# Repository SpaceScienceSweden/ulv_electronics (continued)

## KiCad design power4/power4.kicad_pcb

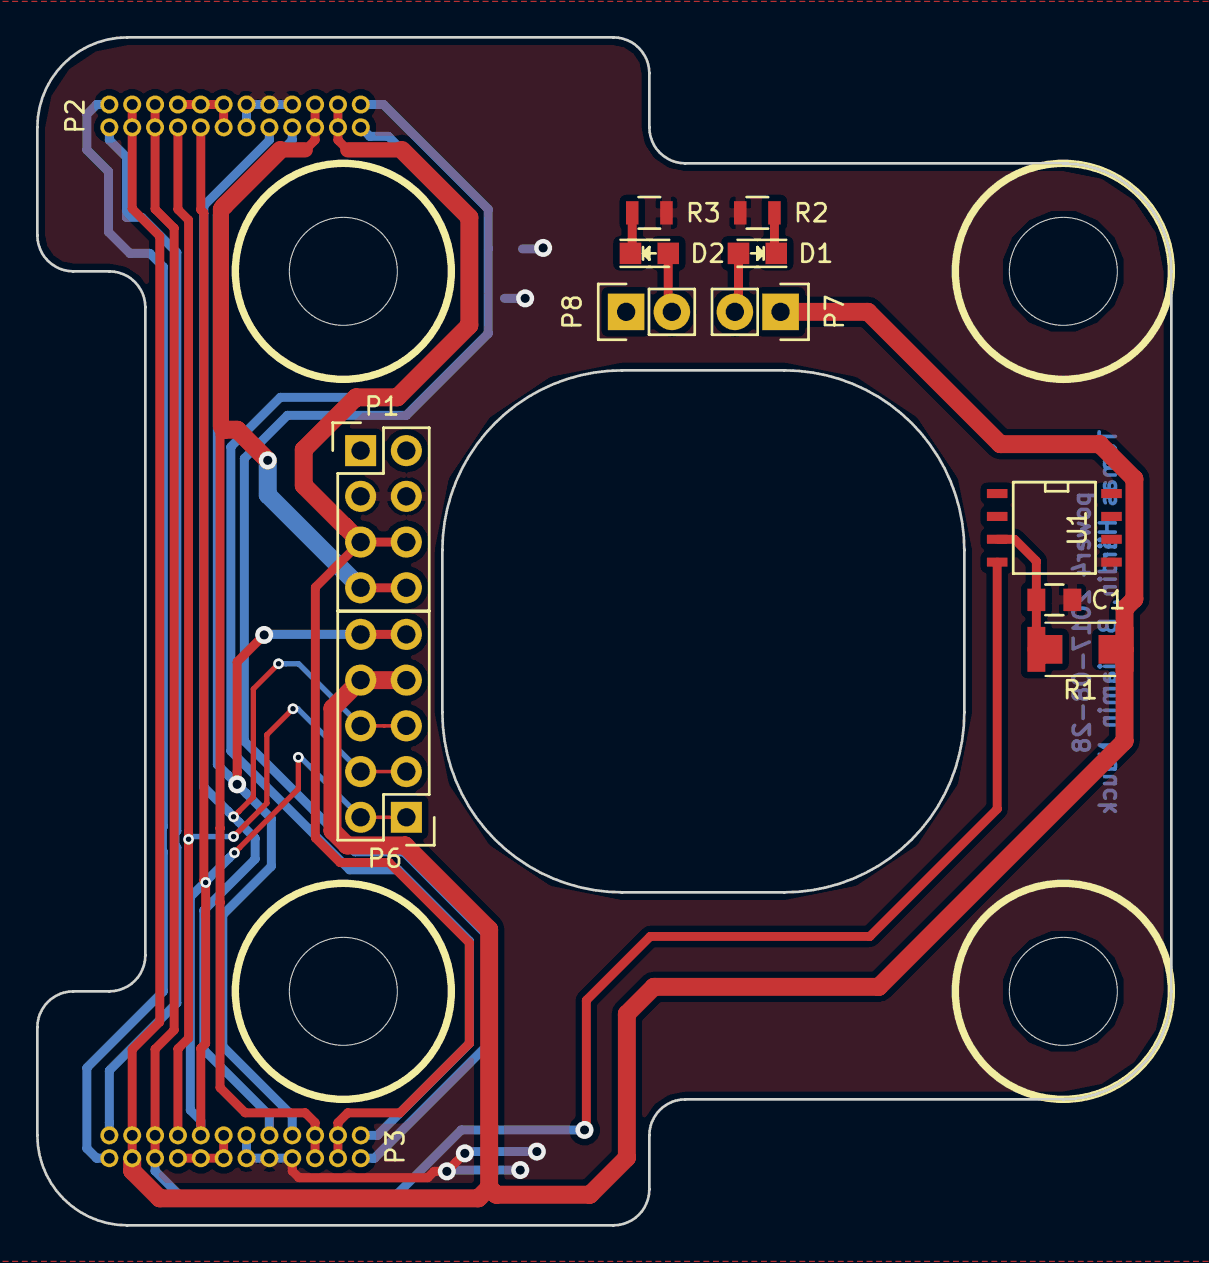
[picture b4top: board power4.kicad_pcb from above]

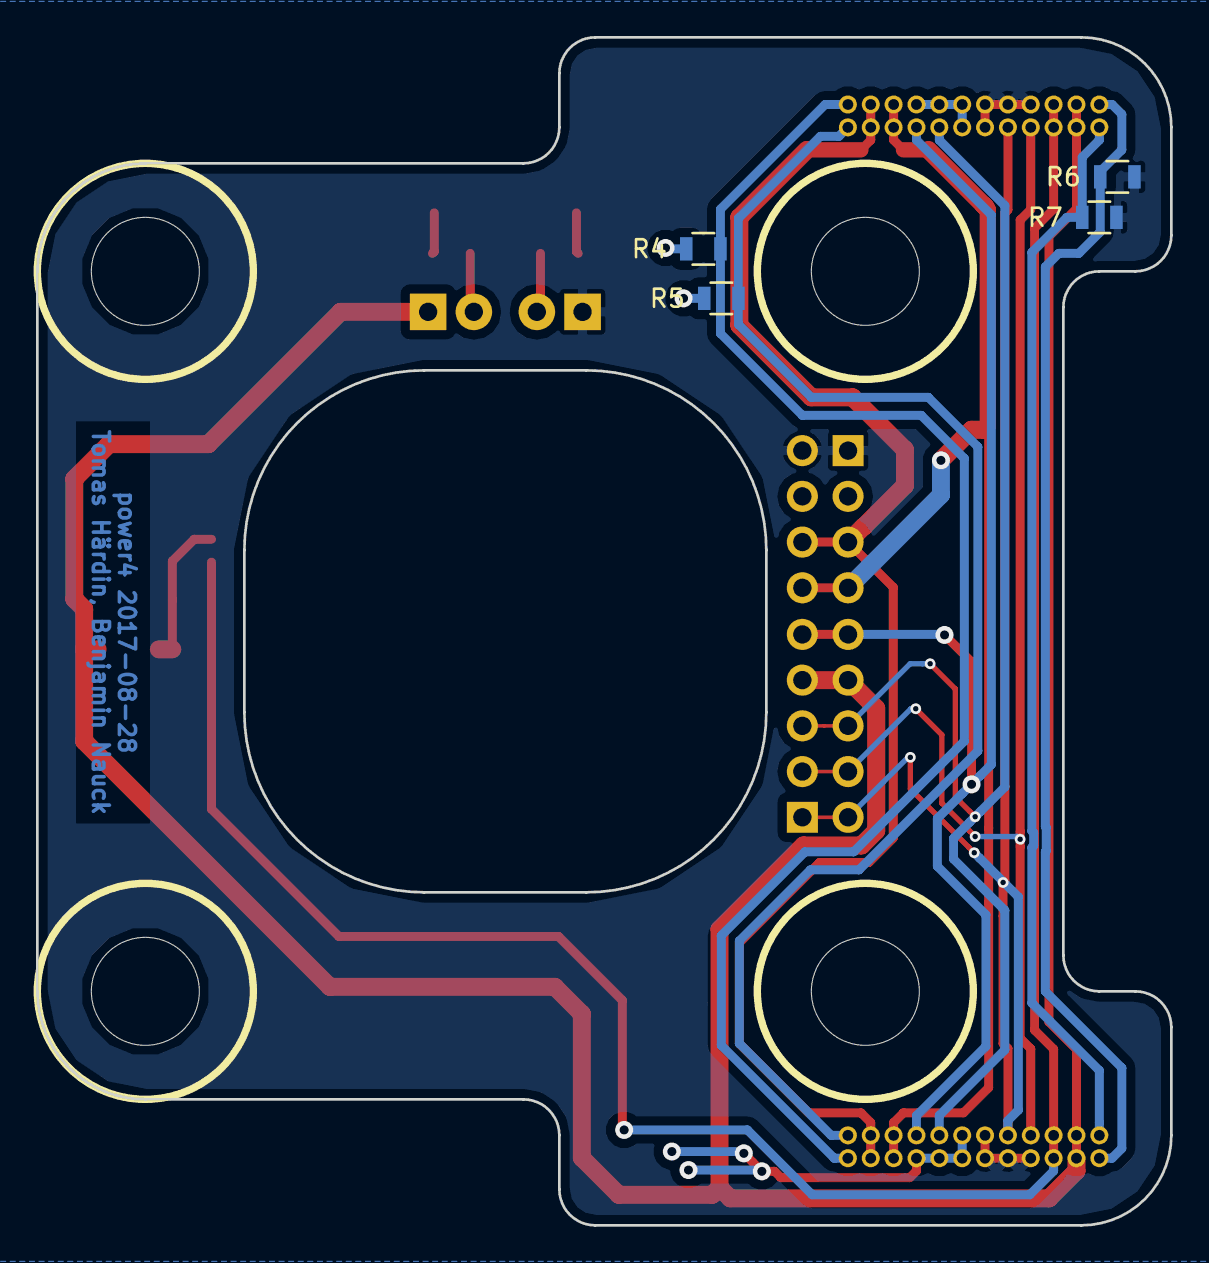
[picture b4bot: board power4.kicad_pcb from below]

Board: 2 copper layers, 63.0 x 66.0 mm, 17 parts (4 on the bottom side), 19 nets.

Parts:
C1: 10u; C_0805
D1, D2: LED; LED_0805
P1: LANDER; Pin_Header_Straight_2x04
P2, P3: CONN_02X12; FTSH-112-04-L-D-RA
P6: PROG; Pin_Header_Straight_2x05
P7, P8: CONN_01X02; Pin_Header_Straight_1x02
R1: 120; Resistor_1206_2010_combined
R2: 1k3; R_0805
R3: 22k; R_0805
R4, R5, R6, R7: 0; R_0805
U1: DS18B20Z; SOIC-8-N

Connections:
+3V3: P2.3, P2.4, P3.21, P3.22, P6.7, P6.8, P7.1, R1.1
//RESET: P2.17, P3.7, P6.9, P6.10
/A: P1.5, P1.6, P2.21, P2.22, P3.3, P3.4
/B: P1.7, P1.8, P2.19, P2.20, P3.5, P3.6
/ONEWIRE: P2.5, P2.6, P3.19, P3.20, U1.4
/PDI: P2.7, P3.17, P6.3, P6.4
/PDO: P2.9, P3.15, P6.1, P6.2
/SCK: P2.15, P3.9, P6.5, P6.6
/VLANDER: P1.1, P1.2, P2.8, P2.10, P2.11, P2.12, P3.13, P3.14, P3.16, P3.18, P8.1, R6.1, R7.1
GND: C1.1, P1.3, P1.4, P2.13, P2.14, P2.16, P2.18, P3.8, P3.10, P3.11, P3.12, R2.2, R3.2, R4.2, R5.2, U1.5
unnamed: C1.2, R1.2, U1.3
unnamed: D1.1, R2.1
unnamed: D1.2, P7.2
unnamed: D2.1, R3.1
unnamed: D2.2, P8.2
unnamed: P2.1, P3.23, R7.2
unnamed: P2.2, P3.24, R6.2
unnamed: P2.23, P3.1, R5.1
unnamed: P2.24, P3.2, R4.1

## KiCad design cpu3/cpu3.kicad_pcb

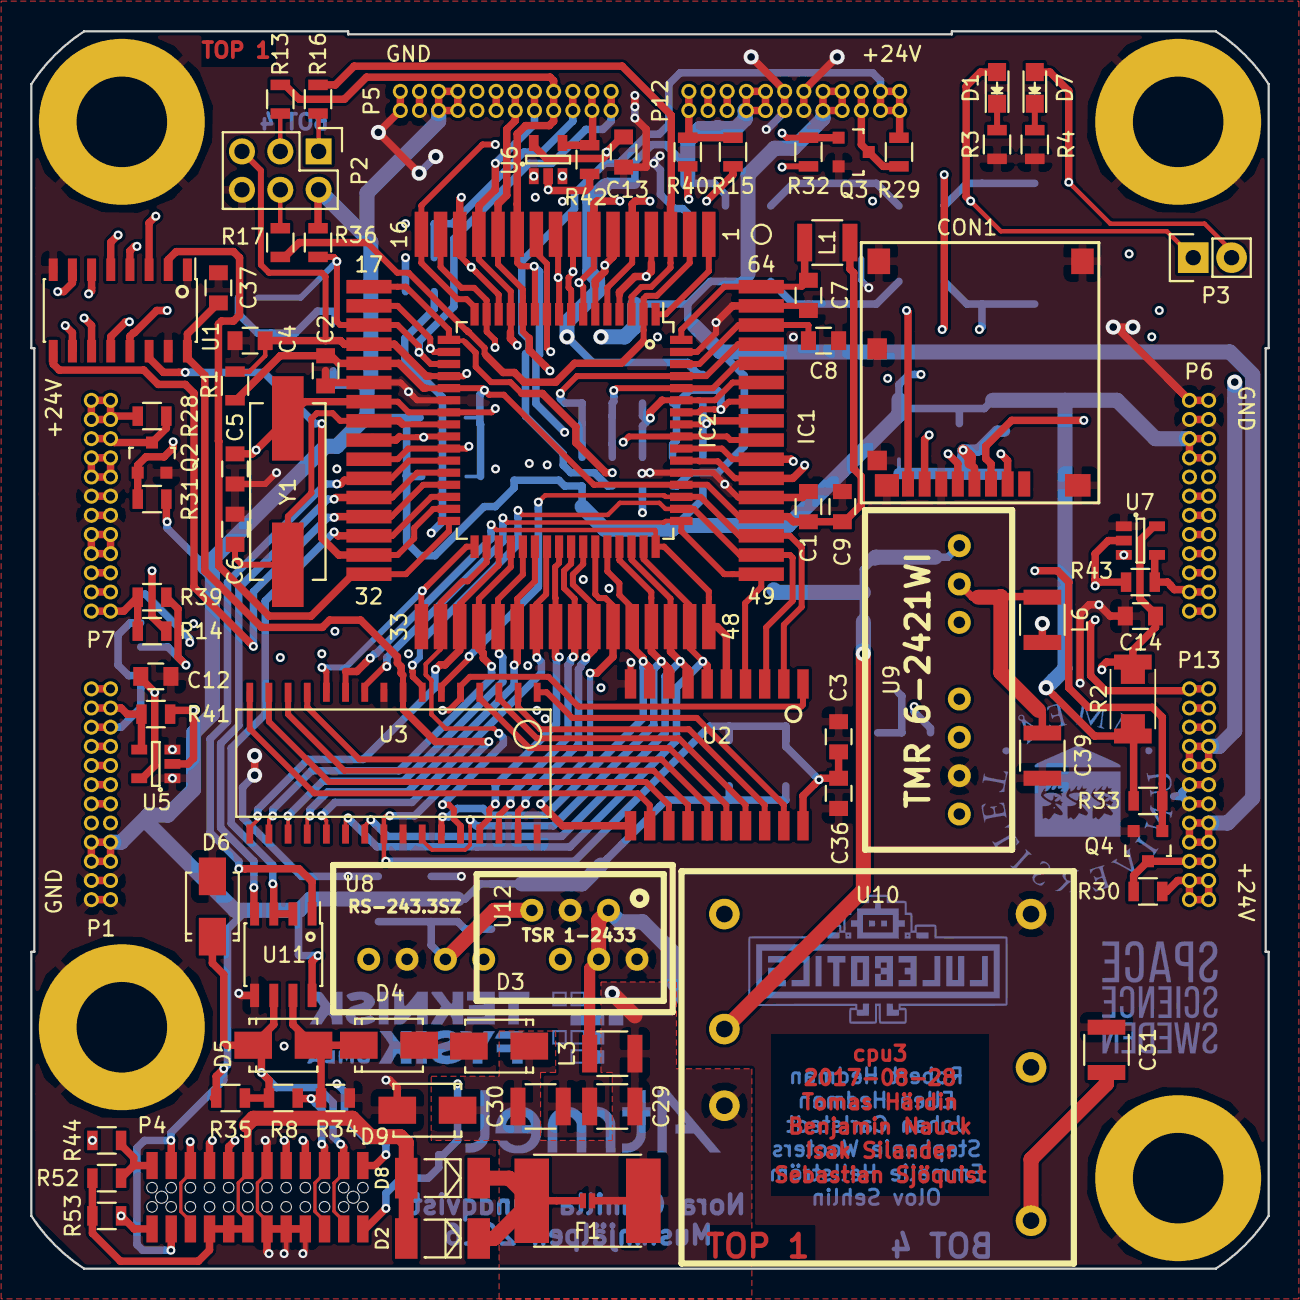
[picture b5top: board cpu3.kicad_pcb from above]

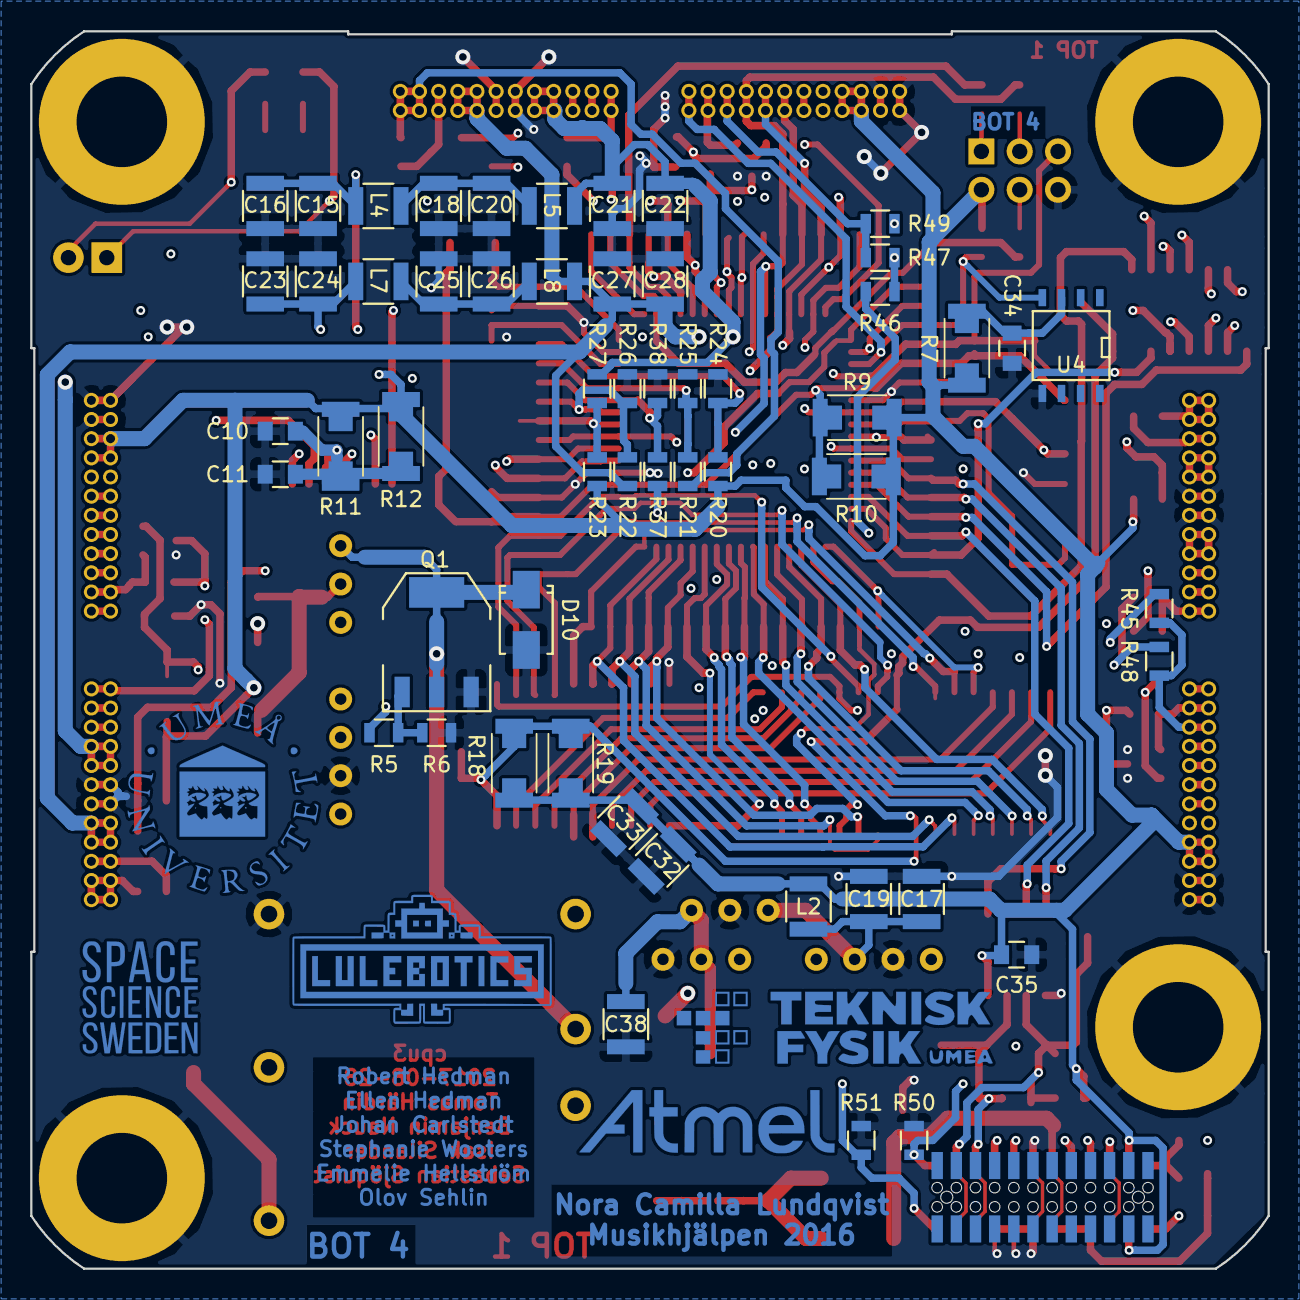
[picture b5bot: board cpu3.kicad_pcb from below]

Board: 4 copper layers, 82.0 x 82.0 mm, 145 parts (55 on the bottom side), 116 nets.

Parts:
C1, C2, C3, C4, C7, C8, C11, C12, C13, C14, C35, C37: 100n; C_0805
C5, C6: 22p; C_0805
C9, C10, C34, C36: 10u; C_0805
C15, C16, C17, C18, C19, C20, C21, C22, C23, C24, C25, C26, C27, C28, C29, C30, C31, C32, C33, C38, C39: 10u; C_1210
CON1: 502774-0891; Molex_502774-0891
D1, D7: LED_Small; LED_0805
D2, D8: SMS240; MELF_Standard
D3, D9, D10: 40V; SMA_Standard
D4, D5, D6: 12V; SMA_Standard
F1: Polyfuse_Small; Fuse_SMD2920
IC1: ATMEGA128L-8AN; ATmegaS128
IC2: ATMEGA128L-8AN; TQFP-64_14x14mm_Pitch0.8mm
L1, L2, L3, L4, L5, L6, L7, L8: 10u; C_1210
P1, P5, P6, P7, P12, P13: CONN_02X12; FTSH-112-04-L-D-RA
P2: ISP; Pin_Header_Straight_2x03
P3: CONN_01X02; Pin_Header_Straight_1x02
P4: CONN_02X12; LPPB122NFSP-RC-holes-backpads
P8, P9, P10, P11: M6; M6_PTH
P14: FUSE_BYPASS; solder_bridge_1mm
Q1: IRLL024NPBF; SOT-223
Q2, Q3, Q4: PMBF170; SOT-23
R1, R5, R23, R25, R26, R38: 10k; R_0805
R2: 100; Resistor_1206_2010_combined
R3, R4: 1k2; R_0805
R6: 1M; R_0805
R7: 120; Resistor_1206_2010_combined
R8, R13, R16, R17: 120; R_0805
R9, R10, R11, R12, R18, R19: 22; Resistor_1206_2010_combined
R14, R15, R39, R40, R41, R42, R43, R44, R45, R46, R47, R48, R49, R50, R51, R52, R53: 0; R_0805
R20, R22, R24: 18k; R_0805
R21, R37: 150k; R_0805
R27: 22k; R_0805
R28, R29, R30, R31, R32, R33: 56k; R_0805
R34, R35: 360; R_0805
R36: 4k7; R_0805
U1: CD74AC153M96; SOIC-16_3.9x9.9mm_Pitch1.27mm
U2: SN74AHC573; SO-20
U3: 71V124SA12YGI; SOJ-32
U4: DS18B20Z; SOIC-8-N
U5, U6, U7: SN74LVC1G125DBVR; SOT-23-5
U8: RS-243.3SZ; RSO-2412D_v2
U9: TMR 6-2421WI; RSO-2412D_v2
U10: THN_30-2415
U11: MAX485; SOIC-8_3.9x4.9mm_Pitch1.27mm
U12: TSR 1-2433; TSR_1
Y1: 7.3728 MHz; Crystal_HC49-SD_SMD

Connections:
+3V3: C32.1, C33.1, C35.1, L2.2, P1.5, P1.6, P1.7, P1.8, P2.2, P4.3, P4.4, P5.5, P5.6, P5.7, P5.8, P6.5, P6.6, P6.7, P6.8, R2.1, R7.1, R9.1, R10.1, R11.1, R12.1, R18.2, R19.2, R20.1, R23.1, R31.1, R32.1, R33.1, R35.2, R36.1, U11.8
+5V: C27.2, C28.2, L8.1, P7.15, P7.16, P7.17, P7.18, P12.15, P12.16, P12.17, P12.18, P13.15, P13.16, P13.17, P13.18, R22.1
+24V: C31.1, P7.21, P7.22, P7.23, P7.24, P12.21, P12.22, P12.23, P12.24, P13.21, P13.22, P13.23, P13.24, R21.1, R28.1, R29.1, R30.1, U10.3
-5V: C21.1, C22.1, L5.2, P7.7, P7.8, P7.9, P7.10, P12.7, P12.8, P12.9, P12.10, P13.7, P13.8, P13.9, P13.10, R27.2
/CS_ADC0: P1.19, P1.20, R45.2, R48.1
/CS_ADC1: P5.19, P5.20, R47.2, R49.2
/CS_ADC2: IC1.54, IC2.54, P6.19, P6.20
/CS_VGND0: IC1.4, IC2.4, P7.3, P7.4
/CS_VGND1: IC1.5, IC2.5, P12.3, P12.4
/CS_VGND2: IC1.6, IC2.6, P13.3, P13.4
/DRDY0: P1.11, P1.12, U1.6
/DRDY1: P5.11, P5.12, U1.5
/DRDY2: P6.11, P6.12, U1.4
/EN_XMEM: IC1.18, IC2.18, U2.1, U3.5
/RD: IC1.34, IC2.34, U3.28
/RESET: C4.1, IC1.20, IC2.20, P2.5, P4.18, R1.1
/SD_CS: CON1.2, IC1.14, IC2.14
/WR: IC1.33, IC2.33, U3.12
/power/A: D5.1, D6.1, P4.21, P4.22, R8.2, R35.1, U11.6
/power/B: D4.1, D5.2, P4.19, P4.20, R8.1, R34.2, U11.7
/power/EN_24V_5V: IC1.10, IC2.10, R5.2
/power/RS485_DE: IC1.30, IC2.30, U11.2, U11.3
/power/RS485_RX: IC1.27, IC2.27, U11.1
/power/RS485_TX: IC1.28, IC2.28, U11.4
/power/VLANDER: D2.2, D8.2, P4.7, P4.9, P4.11, P4.12, R52.2, R53.2
A8: IC1.35, IC2.35, U3.17
A9: IC1.36, IC2.36, U3.18
A10: IC1.37, IC2.37, U3.19
A11: IC1.38, IC2.38, U3.20
A12: IC1.39, IC2.39, U3.21
A13: IC1.40, IC2.40, U3.29
A14: IC1.41, IC2.41, U3.30
A15: IC1.42, IC2.42, U3.31
AD0: IC1.51, IC2.51, U2.2, U3.6
AD1: IC1.50, IC2.50, U2.3, U3.7
AD2: IC1.49, IC2.49, U2.4, U3.10
AD3: IC1.48, IC2.48, U2.5, U3.11
AD4: IC1.47, IC2.47, U2.6, U3.22
AD5: IC1.46, IC2.46, U2.7, U3.23
AD6: IC1.45, IC2.45, U2.8, U3.26
AD7: IC1.44, IC2.44, U2.9, U3.27
ALE: IC1.43, IC2.43, U2.11
EN_VGND0: P7.1, P7.2, R14.2, R39.1
EN_VGND1: P12.1, P12.2, R15.2, R40.2
EN_VGND2: IC1.7, IC2.7, P13.1, P13.2, R14.1, R15.1
EXTRA1: P4.1, R53.1, U1.3
EXTRA2: P4.2, R44.2, R52.1
EXTRA3: P4.24, R46.2, R50.2
EXTRA4: P4.23, R51.2, U1.13
GND: C1.2, C2.2, C3.2, C4.2, C5.1, C6.1, C7.2, C8.2, C9.2, C10.2, C11.2, C12.1, C13.1, C14.1, C15.2, C16.2, C17.2, C18.2, C19.2, C20.2, C21.2, C22.2, C23.1, C24.1, C25.1, C26.1, C27.1, C28.1, C29.2, C30.2, C31.2, C32.2, C33.2, C34.2, C35.2, C36.2, C37.2, C38.2, C39.2, CON1.6, CON1.9, D3.2, D4.2, D6.2, D9.2, D10.2, IC1.22, IC1.53, IC1.63, IC2.22, IC2.53, IC2.63, P1.1, P1.2, P1.3, P1.4, P2.6, P4.13, P4.14, P4.15, P4.17, P5.1, P5.2, P5.3, P5.4, P6.1, P6.2, P6.3, P6.4, P7.11, P7.12, P7.13, P7.14, P8.1, P9.1, P10.1, P11.1, P12.11, P12.12, P12.13, P12.14, P13.11, P13.12, P13.13, P13.14, Q1.3, Q2.2, Q3.2, Q4.2, R3.2, R4.2, R6.1, R24.2, R25.2, R26.2, R34.1, R38.2, R50.1, R51.1, U1.1, U1.8, U1.15, U2.10, U3.9, U3.25, U3.32, U4.5, U5.1, U5.3, U6.1, U6.3, U7.1, U7.3, U8.1, U8.7, U9.7, U10.5, U11.5, U12.2
MISO: CON1.7, IC1.13, IC2.13, P1.15, P1.16, P5.15, P5.16, P6.15, P6.16
MOSI: CON1.3, IC1.12, IC2.12, P1.13, P1.14, P5.13, P5.14, P6.13, P6.14
unnamed: C1.1, C2.1, C9.1, IC1.21, IC1.52, IC2.21, IC2.52, L1.1, R1.2, R9.2, R10.2
unnamed: C6.2, IC1.24, IC2.24, Y1.2
unnamed: C7.1, IC1.64, IC2.64, L1.2
unnamed: C8.1, IC1.62, IC2.62
unnamed: C10.1, C11.1, CON1.4, R11.2, R12.2
unnamed: C12.2, C13.2, C14.2, R2.2, U5.5, U6.5, U7.5
unnamed: C15.1, C16.1, L4.1, U9.8
unnamed: C17.1, C19.1, L2.1, U8.6, U12.3
unnamed: C18.1, C20.1, L4.2, L5.1
unnamed: C23.2, C24.2, L7.2, U9.6
unnamed: C25.2, C26.2, L7.1, L8.2
unnamed: C34.1, R7.2, U4.3
unnamed: C38.1, L3.1, U8.2, U12.1
unnamed: C39.1, L6.2, U9.2
unnamed: D1.1, R3.1
unnamed: D2.1, D8.1, F1.2, P14.1
unnamed: D7.1, R4.1
unnamed: D10.1, Q1.2, Q1.4, U9.1, U10.2
unnamed: IC1.1, IC2.1
unnamed: IC1.2, IC2.2, R17.1
unnamed: IC1.3, IC2.3, R16.1
unnamed: IC1.9, IC2.9, U1.7
unnamed: IC1.25, IC2.25, R44.1, R45.1
unnamed: IC1.26, IC2.26, R46.1, R47.1
unnamed: IC1.29, IC2.29, U1.9
unnamed: IC1.31, IC2.31, U1.14
unnamed: IC1.32, IC2.32, U1.2
unnamed: IC1.57, IC2.57, R23.2, R27.1
unnamed: IC1.58, IC2.58, R22.2, R26.1
unnamed: IC1.59, IC2.59, R37.2, R38.1
unnamed: IC1.60, IC2.60, R21.2, R25.1
unnamed: IC1.61, IC2.61, R20.2, R24.1
unnamed: P1.21, P1.22, R41.1, U5.4
unnamed: P5.21, P5.22, R42.1, U6.4
unnamed: P6.21, P6.22, R43.1, U7.4
unnamed: P7.19, P7.20, Q2.3, R28.2
unnamed: P12.19, P12.20, Q3.3, R29.2
unnamed: P13.19, P13.20, Q4.3, R30.2
unnamed: Q1.1, R5.1, R6.2
unnamed: U2.12, U3.16
unnamed: U2.13, U3.15
unnamed: U2.14, U3.14
unnamed: U2.15, U3.13
unnamed: U2.16, U3.4
unnamed: U2.17, U3.3
unnamed: U2.18, U3.2
unnamed: U2.19, U3.1
ONEWIRE: IC1.19, IC2.19, P1.23, P1.24, P4.5, P4.6, P5.23, P5.24, P6.23, P6.24, R36.2, U4.4
PDI: P2.4, P4.8, R17.2
PDO: P2.1, P4.10, R16.2
PF5: D1.2, IC1.56, IC2.56, P3.1, R39.2, R48.2
PF6: D7.2, IC1.55, IC2.55, P3.2, R40.1, R49.1
PWM0: IC1.15, IC2.15, Q2.1, R31.2
PWM1: IC1.16, IC2.16, Q3.1, R32.2
PWM2: IC1.17, IC2.17, Q4.1, R33.2
SCLK: CON1.5, IC1.11, IC2.11, P1.17, P1.18, P5.17, P5.18, P6.17, P6.18, R13.1
SCLK_OUT: P2.3, P4.16, R13.2
SD_IRQ: CON1.8, IC1.8, IC2.8
TACH0: P7.5, P7.6, U1.10
TACH1: P12.5, P12.6, U1.11
TACH2: P13.5, P13.6, U1.12
VCC: C3.1, C36.1, C37.1, R18.1, R19.1, U1.16, U2.20, U3.8, U3.24
VIN: C29.1, C30.1, D3.1, D9.1, F1.1, L3.2, L6.1, P14.2, R37.1, U10.1
f_ADC: C5.2, IC1.23, IC2.23, R41.2, R42.2, R43.2, U5.2, U6.2, U7.2, Y1.1

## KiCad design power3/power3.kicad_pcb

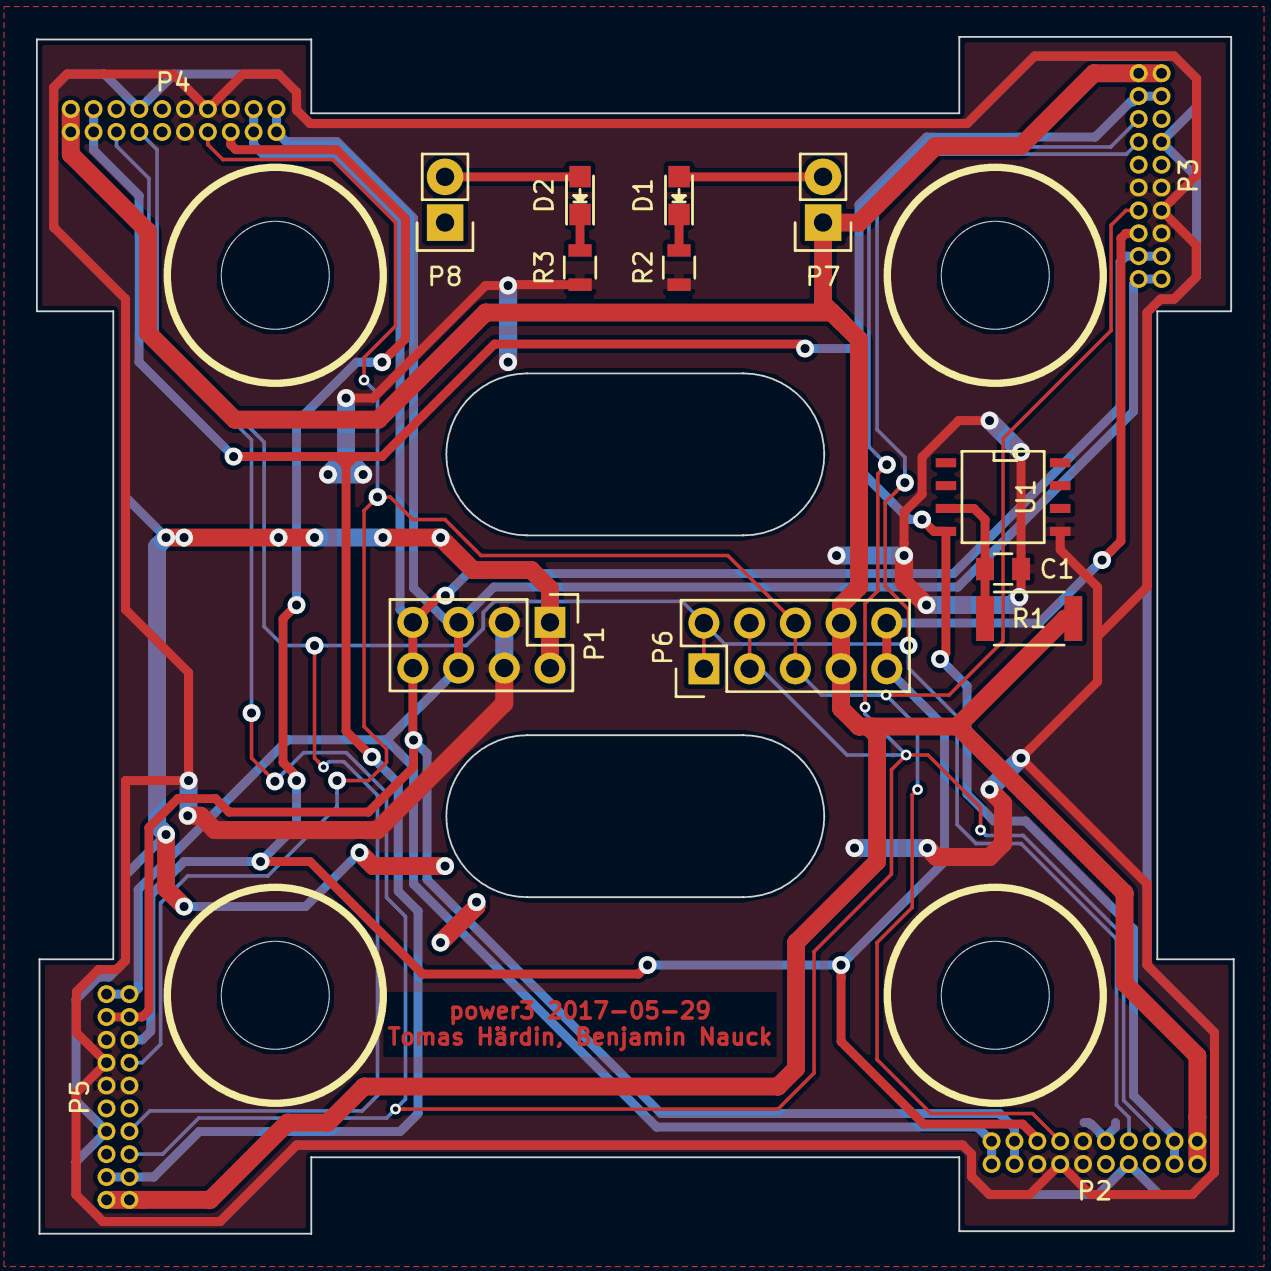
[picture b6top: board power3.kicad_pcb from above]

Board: 2 copper layers, 66.5 x 66.5 mm, 15 parts (0 on the bottom side), 15 nets.

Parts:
C1: 100n; C_0805
D1, D2: LED; LED_0805
P1: LANDER; Pin_Header_Straight_2x04
P2, P3, P4, P5: CONN_02X10; FTSH-110-01-L-D-RA
P6: PROG; Pin_Header_Straight_2x05
P7, P8: CONN_01X02; Pin_Header_Straight_1x02
R1: 130; R_2010
R2: 1k3; R_0805
R3: 22k; R_0805
U1: DS18B20Z; SOIC-8-N

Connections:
+3V3: P2.1, P2.2, P3.1, P3.2, P4.1, P4.2, P5.1, P5.2, P6.7, P6.8, P7.1, R1.1
//RESET: P2.15, P3.15, P4.15, P5.15, P6.9, P6.10
/A: P1.5, P1.6, P2.19, P2.20, P3.19, P3.20, P4.19, P4.20, P5.19, P5.20
/B: P1.7, P1.8, P2.17, P2.18, P3.17, P3.18, P4.17, P4.18, P5.17, P5.18
/ONEWIRE: P2.3, P2.4, P3.3, P3.4, P4.3, P4.4, P5.3, P5.4, U1.4
/PDI: P2.5, P3.5, P4.5, P5.5, P6.3, P6.4
/PDO: P2.7, P3.7, P4.7, P5.7, P6.1, P6.2
/SCK: P2.13, P3.13, P4.13, P5.13, P6.5, P6.6
/VLANDER: P1.1, P1.2, P2.6, P2.8, P2.9, P2.10, P3.6, P3.8, P3.9, P3.10, P4.6, P4.8, P4.9, P4.10, P5.6, P5.8, P5.9, P5.10, P8.1
GND: C1.1, P1.3, P1.4, P2.11, P2.12, P2.14, P2.16, P3.11, P3.12, P3.14, P3.16, P4.11, P4.12, P4.14, P4.16, P5.11, P5.12, P5.14, P5.16, R2.2, R3.2, U1.5
unnamed: C1.2, R1.2, U1.3
unnamed: D1.1, R2.1
unnamed: D1.2, P7.2
unnamed: D2.1, R3.1
unnamed: D2.2, P8.2

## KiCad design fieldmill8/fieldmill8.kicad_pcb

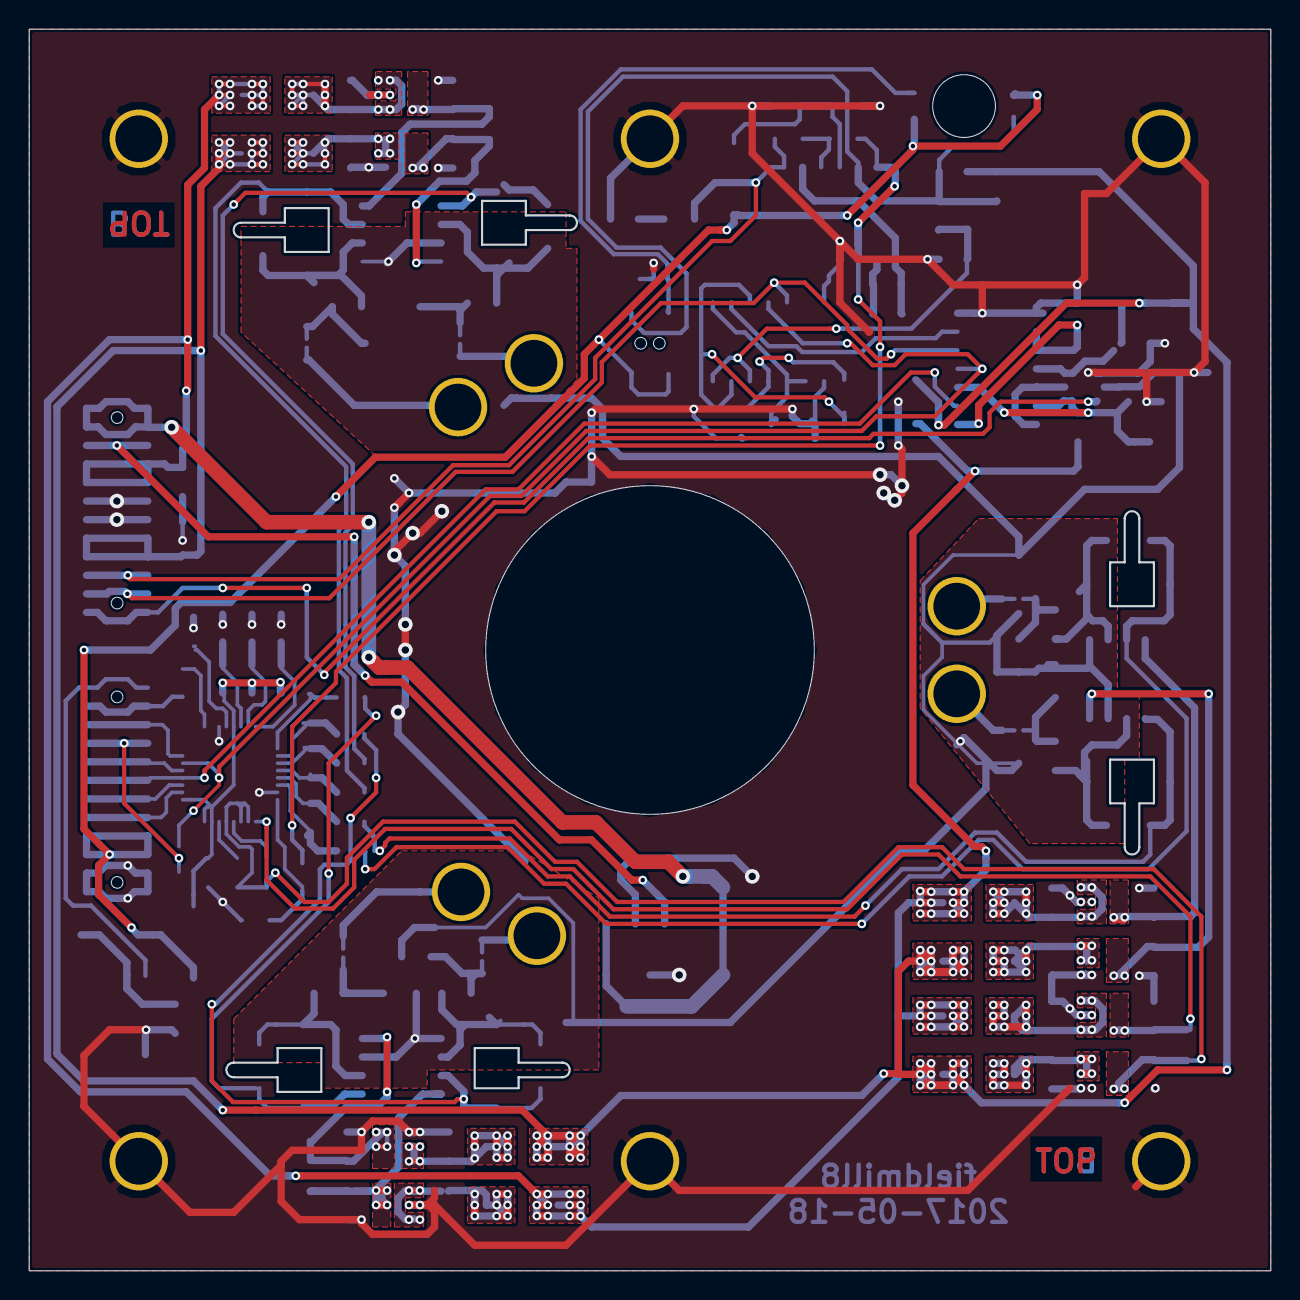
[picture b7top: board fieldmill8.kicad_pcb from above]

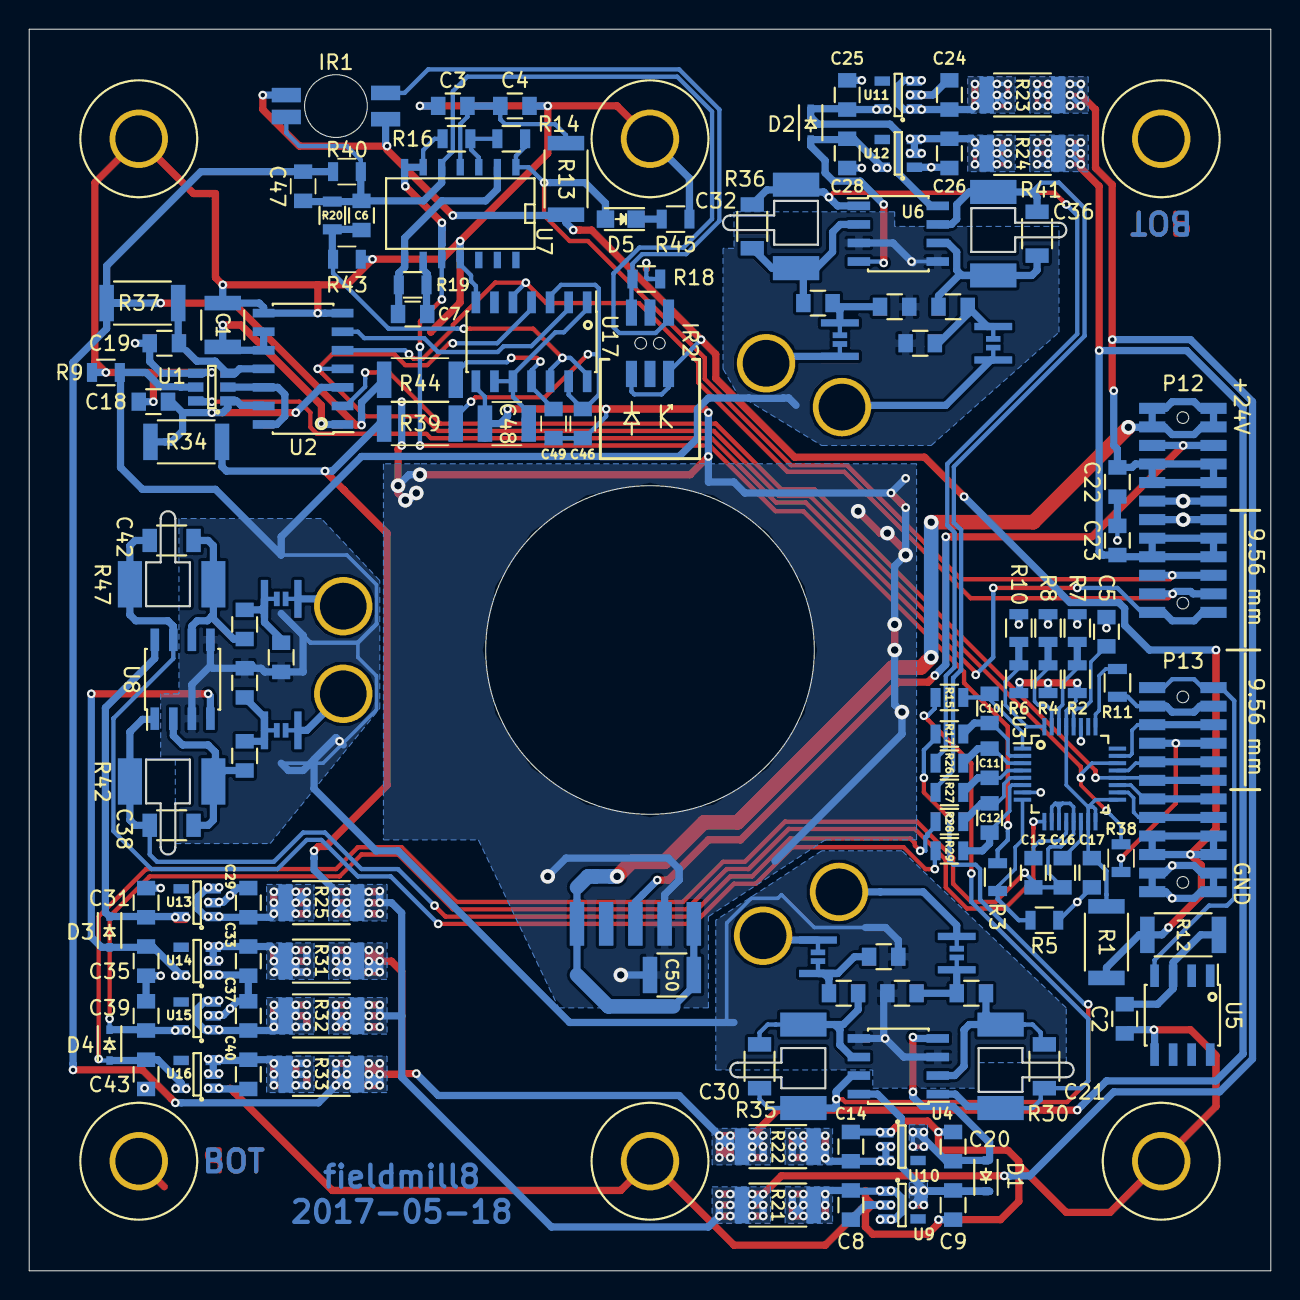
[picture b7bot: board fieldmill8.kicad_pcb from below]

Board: 2 copper layers, 85.0 x 85.0 mm, 153 parts (141 on the bottom side), 92 nets.

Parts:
C1, C48: 33u; C_1210
C2, C4, C7, C8, C9, C14, C18, C19, C20, C22, C23, C24, C25, C26, C28, C29, C31, C33, C35, C37, C39, C40, C43, C46, C49: 10u; C_0805
C3: 100n; C_0805
C5, C13, C16, C17: 1u; C_0805
C6: 470p; C_0805
C10, C11, C12: 1n; C_0805
C15, C27, C34, C41, C44, C45: 4p7; C_0805
C21, C30, C32, C36, C38, C42: 1p; C_1206
C47: open; C_0805
C50: 10u; C_1210
D1, D2, D3, D4: TDZ5V6J; SOD-323
D5: LED; LED_0805
IR1: SG-2BC
IR2: ITR20001; LPPB032NFSP-RC-ITR20001
L1, L3, L5, L7, L9, L11: 470n; C_0805
L2, L4, L6, L8, L10, L12: 19n4; 0806SQ-19N
P1, P2, P3, P4, P5, P6: SENSOR; M3_PTH
P7, P8, P9, P10, P26, P27: M3; M3_FM_PTH
P11: CONN_01X05; MOTOR_SMD
P12, P13: CONN_02X12; LPPB122NFSP-RC
R1: 150; R_2010
R2, R4, R6, R7, R8, R10: 470; R_0805
R3, R5, R9, R15, R17, R19, R26, R27, R28, R29: 10k; R_0805
R11, R38: 50; R_0805
R12: 120; R_2010
R13: 56; R_2010
R14: 1M; R_0805
R16: 1k; R_0805
R18: 680; R_0805
R20: 100k; R_0805
R21, R22, R23, R24, R25, R31, R32, R33: 270; R_2010
R30, R35, R36, R41, R42, R47: 100M; Resistor_2010_2512_combined
R34, R37, R39, R44: 390; R_2010
R40: open; R_0805
R43: 0; R_0805
R45: 1k2; R_0805
R46, R48, R49, R50, R51, R52: 0; solder_bridge_1mm
U1: ADG601; SOT-23-6
U2, U17: MAX504; SOIC-14_3.9x8.7mm_Pitch1.27mm
U3: ADS131A04; LQFP-32_5x5mm_Pitch0.5mm
U4, U6, U8: LTC6241IS8#PBF; SOIC-8_3.9x4.9mm_Pitch1.27mm
U5: DS18B20Z; SOIC-8_3.9x4.9mm_Pitch1.27mm
U7: MAX44252ASD+; SOIC-14_N
U9, U11, U13, U15: ADM7160; SOT-23-5
U10, U12, U14, U16: ADP7182; SOT-23-5

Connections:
+3V3: IR1.A, IR1.C, IR2.A, IR2.C, P13.17, P13.18, P13.19, P13.20, R1.1, R12.2, R13.2
+5V: C22.1, P12.7, P12.8, P12.9, P12.10, R21.2, R23.2, R25.2, R32.2, R34.1, R39.1
+24V: C50.1, P11.1, P11.5, P12.1, P12.2, P12.3, P12.4
-5V: C23.2, C47.2, P12.15, P12.16, P12.17, P12.18, R22.2, R24.2, R31.2, R33.2, R37.2, R40.2, R44.2
//CS_ADC: P13.5, P13.6, U3.23
//DONE: P13.15, P13.16, U3.18
//DRDY: P13.13, P13.14, U3.19
/CS_DACS: P12.21, P12.22, U2.5, U17.5
/EN_VGND: P12.23, P12.24, U1.6
/ITACH: D5.2, P12.19, P12.20, R14.2, U7.1
/MISO: P13.9, P13.10, U3.21
/MOSI: P13.11, P13.12, U2.2, U3.20
/ONEWIRE: P13.1, P13.2, U5.4
/PWM: P11.3, P12.5, P12.6
/Tachometers/DIN: U2.6, U17.2
/Tachometers/RAW_ITACH: R3.2, R16.1, U7.6, U7.7, U7.10
/channel1/+2V5: C9.1, D1.1, U4.8, U9.5
/channel1/-2V5: C20.1, D1.2, U4.4, U10.5
/channel1/OUT+: C30.2, R17.1, R35.2, U4.7
/channel1/OUT-: C21.2, R15.2, R30.2, U4.1
/channel1/SENSORN: L2.1, P2.1, R46.2
/channel1/SENSORP: L4.1, P1.1, R48.1
/channel2/+2V5: C25.1, D2.1, U6.8, U11.5
/channel2/-2V5: C28.1, D2.2, U6.4, U12.5
/channel2/OUT+: C36.2, R27.1, R41.2, U6.7
/channel2/OUT-: C32.2, R26.2, R36.2, U6.1
/channel2/SENSORN: L6.1, P4.1, R49.2
/channel2/SENSORP: L8.1, P3.1, R50.1
/channel3/+2V5: C31.1, D3.1, U8.8, U13.5
/channel3/-2V5: C35.1, D3.2, U8.4, U14.5
/channel3/OUT+: C42.2, R29.1, R47.2, U8.7
/channel3/OUT-: C38.2, R28.2, R42.2, U8.1
/channel3/SENSORN: L10.1, P6.1, R51.2
/channel3/SENSORP: L12.1, P5.1, R52.1
/f_ADC: P13.3, P13.4, R11.2
/vreg4/+2V5: C39.1, D4.1, U3.9, U15.5
/vreg4/-2V5: C13.1, C16.2, C43.1, D4.2, U3.10, U3.11, U3.13, U16.5
GND: C1.2, C2.2, C3.2, C4.2, C5.1, C8.2, C9.2, C14.2, C17.2, C18.2, C19.2, C20.2, C22.2, C23.1, C24.2, C25.2, C26.2, C28.2, C29.2, C31.2, C33.2, C35.2, C37.2, C39.2, C40.2, C43.2, C46.2, C48.2, C49.2, C50.2, P7.1, P8.1, P9.1, P10.1, P11.4, P12.11, P12.12, P12.13, P12.14, P13.21, P13.22, P13.23, P13.24, P26.1, P27.1, R5.2, R7.2, R8.2, R9.2, R10.2, R18.2, R43.2, R45.2, U1.4, U2.7, U2.8, U3.7, U3.27, U5.5, U7.11, U9.2, U10.1, U11.2, U12.1, U13.2, U14.1, U15.2, U16.1, U17.7, U17.8
unnamed: C1.1, U2.1, U2.9, U2.10
unnamed: C2.1, R12.1, U5.3
unnamed: C3.1, C4.1, R13.1, U7.4
unnamed: C5.2, U3.28
unnamed: C6.1, R20.2, R43.1, U17.12, U17.14
unnamed: C7.1, R19.1, U7.2, U7.8
unnamed: C7.2, R19.2, U7.9
unnamed: C8.1, R21.1, U9.1, U9.3
unnamed: C10.1, R15.1, U3.1
unnamed: C10.2, R17.2, U3.2
unnamed: C11.1, R26.1, U3.3
unnamed: C11.2, R27.2, U3.4
unnamed: C12.1, R28.1, U3.5
unnamed: C12.2, R29.2, U3.6
unnamed: C13.2, U3.12
unnamed: C14.1, R22.1, U10.2, U10.3
unnamed: C15.1, L1.1, L2.2, R46.1
unnamed: C16.1, U3.14
unnamed: C18.1, R34.2, U1.1, U2.3, U2.13
unnamed: C19.1, R37.1, U1.3, U2.11
unnamed: C21.1, L1.2, R30.1, U4.2
unnamed: C24.1, R23.1, U11.1, U11.3
unnamed: C26.1, R24.1, U12.2, U12.3
unnamed: C27.2, L3.1, L4.2, R48.2
unnamed: C29.1, R25.1, U13.1, U13.3
unnamed: C30.1, L3.2, R35.1, U4.6
unnamed: C32.1, L5.2, R36.1, U6.2
unnamed: C33.1, R31.1, U14.2, U14.3
unnamed: C34.1, L5.1, L6.2, R49.1
unnamed: C36.1, L7.2, R41.1, U6.6
unnamed: C37.1, R32.1, U15.1, U15.3
unnamed: C38.1, L9.2, R42.1, U8.2
unnamed: C40.1, R33.1, U16.2, U16.3
unnamed: C41.2, L7.1, L8.2, R50.2
unnamed: C42.1, L11.2, R47.1, U8.6
unnamed: C44.1, L9.1, L10.2, R51.1
unnamed: C45.2, L11.1, L12.2, R52.2
unnamed: C46.1, R39.2, U17.3, U17.13
unnamed: C6.2, C47.1, IR1.E, IR2.E, R20.1, R40.1, U7.5
unnamed: C48.1, U17.1, U17.9, U17.10
unnamed: C49.1, R44.1, U17.11
unnamed: D5.1, R45.1
unnamed: IR1.K, IR2.K, R18.1
unnamed: P13.7, P13.8, R38.2
unnamed: R2.1, R7.1, U3.30
unnamed: R3.1, R5.1, U3.8
unnamed: R4.1, R8.1, U3.31
unnamed: R6.1, R10.1, U3.32
unnamed: R11.1, U3.25
unnamed: R14.1, R16.2, U7.3
unnamed: U1.2, U2.12, U2.14
SCLK: R38.1, U2.4, U3.22, U17.4
VDD: C17.1, R1.2, R2.2, R4.2, R6.2, U3.15, U3.16, U3.17, U3.29
VGND: C15.2, C27.1, C34.2, C41.1, C44.2, C45.1, R9.1, U1.5, U4.3, U4.5, U6.3, U6.5, U8.3, U8.5

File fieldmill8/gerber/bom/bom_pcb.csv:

Item,Reference(s),Value,Quantity,1st Distrib. Link,1st Distrib. PN,Mfg. Name,Mfg. Part Number
1,C1,33u,1,https://www.elfa.se/sv/kondensator-47-uf-10-vdc-1210-murata-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,165-76-820,Murata,GRM32ER71A476KE15L
2,C10 C11 C12,1n,3,,,,
3,C13 C16 C17 C5,1u,4,,,,
4,C14 C18 C19 C2 C20 C22 C23 C24 C25 C26 C28 C29 C31 C33 C35 C37 C39 C4 C40 C43 C50 C7 C8 C9,10u,24,,,,
5,C15 C27 C34 C41 C44 C45,4p7,6,,,,
6,C21 C30 C32 C36 C38 C42,1p,6,,,,
7,C3,100n,1,,,,
8,C6,470p,1,,,,
9,D1 D2 D3 D4,TDZ5V6J,4,http://se.farnell.com/nxp/tdz5v6j/diode-zener-0-500w-5v6v-so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,2069517,Nexperia,TDZ5V6J
10,D5,LED,1,,,,
11,IR2,ITR20001,1,https://www.elfa.se/sv/reflexdetektor-kodenshi-sg-2bc/p/17534043,175-34-043,,
12,L1 L11 L3 L5 L7 L9,470n,6,http://se.farnell.com/coilcraft/0805ht-r47tglb/inductor-rf-4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,2286480,Coilcraft,0805HT-R47TGLB
13,L10 L12 L2 L4 L6 L8,19n4,6,http://se.farnell.com/coilcraft/0806sq-19nglb/inductor-rf-19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,2286600,Coilcraft,0806SQ-19NGLB
14,P12 P13,CONN_02X12,2,,,,
15,R1,150,1,,,,
16,R10 R8,470,2,,,,
17,R11 R38,50,2,,,,
18,R12,120,1,,,,
19,R13,56,1,,,,
20,R14,1M,1,,,,
21,R15 R17 R19 R26 R27 R28 R29 R3 R5 R9,10k,10,,,,
22,R16,1k,1,,,,
23,R18,680,1,,,,
24,R20,100k,1,,,,
25,R21 R22 R23 R24 R25 R31 R32 R33,270,8,,,,
26,R30 R35 R36 R41 R42 R47,100M,6,http://se.farnell.com/yageo-phycomp/rc2010fk-0710ml/motst-tj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,9235809,,
27,R34 R37,390,2,,,,
28,R43,0,1,,,,
29,R45,1k2,1,,,,
30,U1,ADG601,1,,,,
31,U10 U12 U14 U16,ADP7182,4,,,,
32,U11 U13 U15 U9,ADM7160,4,,,,
33,U2,MAX504,1,,,,
34,U3,ADS131A04,1,,,,
35,U4 U6 U8,LTC6241IS8#PBF,3,http://se.farnell.com/linear-technology/ltc6241cs8-pbf/ic-sm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,1330969,,
36,U5,DS18B20Z,1,,,,
37,U7,MAX44252ASD+,1,,,,
